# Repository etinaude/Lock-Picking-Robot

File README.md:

# 🔑 Unlocked 🔑

## Introduction

### Background

An open source Lock picking robot. Basically, there are many skeleton keys in use (the most common example is the TSA 007, [which is bad](https://www.youtube.com/watch?v=GhESSMvf_to)). Having one key which can open MANY different locks, especially without the lock owners people knowing it exists [or can be bought on Aliexpres for a pound](https://www.aliexpress.com/item/1005006407379398.html). It is a massive security issue. However, the TSA, locksmiths etc need to open locks in certain situations, and if you make locks easy to open for them, they are easy to open for everyone.

### 🔒 ➡️ 🔑🤖 ➡️ 🔓

So, lock-picking robot!!! The idea behind this robot is that it will be able to open difficult-to-pick locks. However, it takes a bit of time. That means you can get a lock which this robot would take 5 min to pick, but would require hundreds of keys (rather than a set of 7), and waiting with a very overt device by a lock for 5 min is a lot more obvious than unlocking it with a key which makes it look like you own the lock. 

### How it works

It feeds wire through a hollow key to press each pin and brute force all possible combinations. So security pins do not affect it since it is not looking for force feedback. However, more pins, or potential cut depths (entropy) make it take exponentially longer, it takes about 0.7s per combo so a 4 pin/4 cut depth lock would take about 3 min, but 5 pin/5 cut depth would take about 35 min to try all combos. So it's possible to design a lock with many security pins and an annoying keyway, very hard to pick for a human, but relatively quick for this robot.

### TLDR:

For lock sports/locksmiths its a fun toy, and for everyone else an interesting alternative to skeleton keys (and stop using TSA locks)

### Demo

## 💻 Software

### Prerequirements
- Arduino IDE
- Git
- Using [openrb board manager](https://raw.githubusercontent.com/ROBOTIS-GIT/OpenRB-150/master/package_openrb_index.json)
- Arduino SAMD Board Manager
- DYNAMIXEL2Arduino Library

Follow [this guide](https://emanual.robotis.com/docs/en/parts/controller/openrb-150/#development-environment) to get everything set up

The Source Code is in the repo, fully open source, if you make any changes (please do!) keep them open source as well (GPL 3.0 licence)

## ⚡ Electronics

### Components

- Servo Motors - [Dynamixel xl330-m288-t](https://emanual.robotis.com/docs/en/dxl/x/xl330-m288/) 
- Driver Board - [openrb-150](https://emanual.robotis.com/docs/en/parts/controller/openrb-150/)

## ⚙️ Mechanics

Unlocked uses FDM, SLA and DMLS parts for different levels of precision and strength, it uses 0.4mm copper wire to press the pins. More details in the `/3D files` Folder

### Tools Required

- FDM 3D printer
- Vat Polymerization 3D printer (DLP/SLA)
- (Ideally) DMLS 3D printer
- General Hand tools

## 📝 Notes

A new key blank will be needed for a different kind of lock based on the number of pins and the keyway, the current one can be modified to fit this, this should be made out of DMLS steel, companies like JLCPCB can print this, or you can use a SLA part which will likely break a few times so you'll a few spare.

### Future developments

- Include a more robust way to test if the lock is unlocked (for now it tilts slightly from gravity) but a current feedback servo would be better
- Use current feedback to create a set of possible sets or false sets to reduce the number of combos to try
- Before brute force try combing first

## 📄 References

- [Original 1991 Mechanical Patent -  US patent 5,172,578](https://www.researchgate.net/figure/S-A-Bitzioss-1991-design-for-a-Sputnik-decoder-pick-for-pin-tumbler-locks-US_fig9_271020041)
- [A good YouTube video of a design also based on the 1991 patent](https://www.youtube.com/watch?v=QE9MT1LG-PU)
- [Physical lock decoder](https://www.youtube.com/watch?v=CLcOZhq2GjQ)

## 💬 Contact Me

[https://etinaude.dev/contact](https://etinaude.dev/contact)

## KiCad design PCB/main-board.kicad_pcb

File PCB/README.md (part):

# PCBs

KiCad 10 project for the **arm board** in [`main-board/`](main-board/). Each arm of the robot has one: an ESP32-S3 SuperMini drives the arm's brushed DC motor and reads the carriage position from a magnet, and talks to the motherboard over CAN. Etienne calls it the "main board"; the schematic title is "Lock Picking Robot - Arm Board" and the firmware env is `arm`. It is not the motherboard.

## Status

- **Schematic:** v2 rev 7: CAN only (the I²C option and JP1–JP3 are gone) and CAN TX/RX moved to GPIO8/GPIO9. Rev 6 re-assigned the GPIOs for U1 at 0° and added TP3. ERC 0 errors (38 pin-type warnings from the EasyEDA symbols). C14 changed to 100 pF on 2026-10-09 (schematic, PCB and JLC BOM all updated; the BOM lists C1546).
- **PCB: rev 7 routed** (2026-10-07). Zones filled; DRC 0 violations, 0 unconnected, parity clean. U1, U2, U3, J2, CN2, H1/H2, the TPs, the outline and both zones are locked. The heat-sink pad over U2 is still missing and must come back smaller than before (see [Layout to-do](#layout-to-do)).
- **Production files** in [`main-board/production/`](main-board/production/) are from rev 5 and don't match the board. Regenerate before ordering.
- **Firmware isn't ready for this board** ([Known issues](#known-issues)).

## At a glance

| | |
|---|---|
| MCU | ESP32-S3 SuperMini (U1) on 2 × 9-pin 2.54 mm female headers, top side |
| Motor driver | TI DRV8876 (U2), PH/EN mode, 1.0 A current limit |
| Position sensor | Melexis MLX90393 (U3) 3-axis magnetometer, centred over the carriage magnet |
| Bus | TI SN65HVD230 CAN transceiver (U5), 120 Ω termination on solder jumper JP4 |
| Power | 12 V in on CN2 → TPS54202 buck (U4) → 5 V → SuperMini (its LDO makes 3.3 V) |
| Board | 24.7 × 23.75 mm with 1 mm corners, plus R 3.2 mm bulges round the two M2 nuts (24.7 × 28.4 mm overall). 2 layers, 1.6 mm FR4, 1 oz |
| Assembly | Bottom side by JLCPCB (Economic PCBA); top side hand-soldered |

## Connectors and pinout

### CN2: 12 V + bus (AMASS XT30APB(2+2)-M, C53065086)

Vertical male, plug enters from the top. Polarised: make sure the cable and the motherboard use the same pin order.

| Pin | Net |
|---|---|
| 4 | +12V |
| 3 | GND (solid to both pours, carries the motor return) |
| 2 | CANH |
| 1 | CANL |

### J2: motor (JST S2B-PH-K-S, side entry, C173752)

Pin 1 = OUT1, pin 2 = OUT2. The body overhangs the board edge by design.

### U1: SuperMini pin map

| Pin | Net | Use |
|---|---|---|
| GPIO1 | DRV_IPROPI | Motor current, ADC1_CH0, 3.3 V/A |
| GPIO2 / 3 / 4 | MAG_SDA / MAG_SCL / MAG_INT | Magnetometer, I²C address 0x0C |
| GPIO5 / 6 / 7 | EXP_IO5 / EXP_IO6 / EXP_IO7 | Spare, on TP1 / TP2 / TP3 |
| GPIO8 | CAN_TX | CAN TX to U5 (R7 pulls it high) |
| GPIO9 | CAN_RX | CAN RX from U5 |
| GPIO10 | DRV_nFAULT | Driver fault, active low (10 k pull-up) |
| GPIO11 | DRV_nSLEEP | Drive **high** to run |
| GPIO12 | DRV_IN2_PH | Direction |
| GPIO13 | DRV_IN1_EN | PWM |
| TX / RX | | Not used. TX prints the ROM boot log at reset |
| 5V / 3V3 | VBUS / +3V3 | VBUS ≈ 4.7 V after D1 |

The pins follow the layout: U1 sits at 0°, so the left header (GPIO1–7) is next to U3 and the right header (GPIO8–13) is next to U2 and CN2. The reasoning is in [`main-board/layout plan.md`](main-board/layout%20plan.md).

GPIOs are 3.3 V only. Test pads TP1, TP2, TP3, TP5 and TP7 (top, 1.5 mm, labelled) carry IO5, IO6, IO7, 3V3 and GND. TP6 (VBUS, labelled 5V) is on the bottom next to the 5V header pin.

## CAN: U5, JP4

- **U5** is hand-soldered on the top under the SuperMini, so fit and test it **before** soldering the headers.
- **Termination:** JP4 ("TERM") is on the bottom under the XT30, between the bus pins, with R5 (120 Ω) beside it. It is open as made and can be bridged after assembly. The whole bus needs exactly two 120 Ω terminations, at its two ends: bridge JP4 on the two end arms only. On every arm it would be about 17 Ω and the bus won't work. Keep the bit rate modest (250 kbit/s).
- **U5 details:** R7 pulls TXD high so a resetting or flashing arm can't hold the bus dominant (GPIO8 floats during boot). R6 (10 kΩ on Rs) selects slope control. C13 decouples VCC.

## Power

- **U4, TPS54202DDCR** (C191884): 4.5–28 V in, 500 kHz synchronous buck.
  - R8/R9 = 75 kΩ / 10 kΩ set 5.07 V. C14 = 100 pF (C1546) feed-forward across R8: TI's Eq. 16 puts its zero at the loop crossover, 1/(2π × 75 kΩ × 100 pF) ≈ 21 kHz, the same corner as the datasheet's 100 kΩ / 75 pF. Rev 7 had 47 pF (45 kHz, above crossover, little phase boost).
  - L1 = 10 µH FTC252012S100MBCA (C5832376). Stock was low (389 on 2026-10-07); fallback SWPA3015S100MT (C45403, needs a 3 × 3 mm footprint).
  - C1 10 µF 25 V in, C2 100 nF BOOT–SW, C3/C4 2 × 47 µF 6.3 V out. Add a third 47 µF (C16780) if the output rings on a load step.
  - **EN floats** on its internal pull-up. It is rated 7 V max, so never tie it to VIN.
- **D1, 1N5819WS:** feeds the SuperMini's 5 V pin and stops its USB back-feeding the buck while programming. It sits outside the right header next to the 5V pin, so the ESP's supply current stays in the top-right corner, away from U3.
- **+3V3** comes from the SuperMini's LDO and feeds U3, the pull-ups, U5 and the DRV8876 VREF.

## Motor driver: U2, DRV8876RGTR

- PMODE and IMODE tied to GND: PH/EN mode, fixed off-time chopping, auto-retry on overcurrent.
- **Current limit:** R1 = 3.3 kΩ gives I_TRIP = 1.0 A, just above the 12 V N30 gearmotor's stall (just under 1 A measured), and IPROPI reads 3.3 V/A. The ESP32 ADC tops out near 3.1 V, so readings cover 0–0.94 A; a reading pinned at full scale means stalled.
- R1 is an 0805 on hand-solder pads so it's easy to swap: 4.7 kΩ gives 0.70 A, 2.2 kΩ gives 1.5 A.
- C12 (10 nF) filters IPROPI. C5/C6 (100 nF + 22 µF) at VM, C7 on VCP, C8 on CPH–CPL. R2 pulls nFAULT up.

## Magnetometer: U3, MLX90393SLW-ABA-011-RE

I²C mode, address 0x0C (A0 = A1 = GND), INT on MAG_INT. The Hall plates are at the package centre, so U3 is centred over the carriage magnet. R3/R4 are 2.2 kΩ pull-ups; C9/C10 100 nF and C11 10 µF decouple it.

## Layout

### Layout to-do

The full placement plan is in [`main-board/layout plan.md`](main-board/layout%20plan.md).

1. ~~Update PCB from Schematic and place.~~ Done. Placement as built:
   - **Bottom, U2:** C5–C8 along the top edge. R2 right under U2, across nFAULT and VREF (3V3). The strip right of U2 is kept clear for EN/PH and the motor return. R1 (0805) stands on the IPROPI line at (24.3, 29.3), IPROPI pad up, so IPROPI runs straight to C12 and IO1 and MAG_SDA passes underneath.
   - **Bottom, buck:** stacked L1 → C1 → U4. C1 straddles the SW trace, which runs up between C1's pads to L1, so the VIN–GND loop is about 2 mm. C3/C4 sit left of L1, C2 left of U4, and R8/C14/R9 in a row under U4's FB pin.
   - **Bottom, other:** D1 outside the right header, VBUS end towards the 5V pin. TP6 right of C8 next to the 5V pin. U3's caps and pull-ups around U3, with C10 beside pin 8 and R4 on SCL by the CS via. R6 by U5's Rs pin and C13 at (28.9, 39.9) beside U5's VCC via. JP4 and R5 under the XT30 between the bus pins, ≥ 0.98 mm from them.
   - **Top, under the SuperMini:** U5 at 90°: TXD/RXD face IO8/IO9 above the TP row, CANH/CANL leave through the IO10/IO9 gap to the CN2 pins.
2. ~~Route.~~ Done, see [Routing](#routing).
3. **Restore the heat-sink pad, smaller.** It was deleted in the `layout` commit (4722493). The old 28.6–32.4 × 23.45–27.85 rectangle now hits the IPROPI via at (28.45, 27.5) and comes within 0.2 mm of the 3V3 trunk at y 28.15. Use **x 28.95–32.4, y 23.45–27.8** (GND, F.Cu + F.Mask), then refill zones and re-run DRC.
4. Run `scripts/generate_production.py --all` and check the analysis output.

### Routing

| Net group | Layer and path | Width |
|---|---|---|
| 12 V motor feed | Top: CN2 +12V up between H1 and the pad, through the 5V/GND header gap, along the top edge to two vias by C5/C7. VM bus C6–C5–C7 on the bottom, a 0.3 mm link between C5 and C7 into pin 9 | 0.6 mm |
| Motor outputs | Bottom, necked to 0.3 mm at U2. OUT2 runs over the top of J2 pin 1 | 0.5 mm |
| Motor return | GND pours. U2's PGND pins and exposed pad sit in the main bottom pour, which runs straight to CN2's GND pin | — |
| Buck | Bottom. C1 onto VIN/GND, SW up between C1's pads to L1 and under U4 to C2, +5V bar L1–C3–C4 | 0.4–0.6 mm |
| 12 V to the buck | Top through the IO13/IO12 gap, via at (33.55, 32.23), bottom into C1 | 0.4 mm |
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
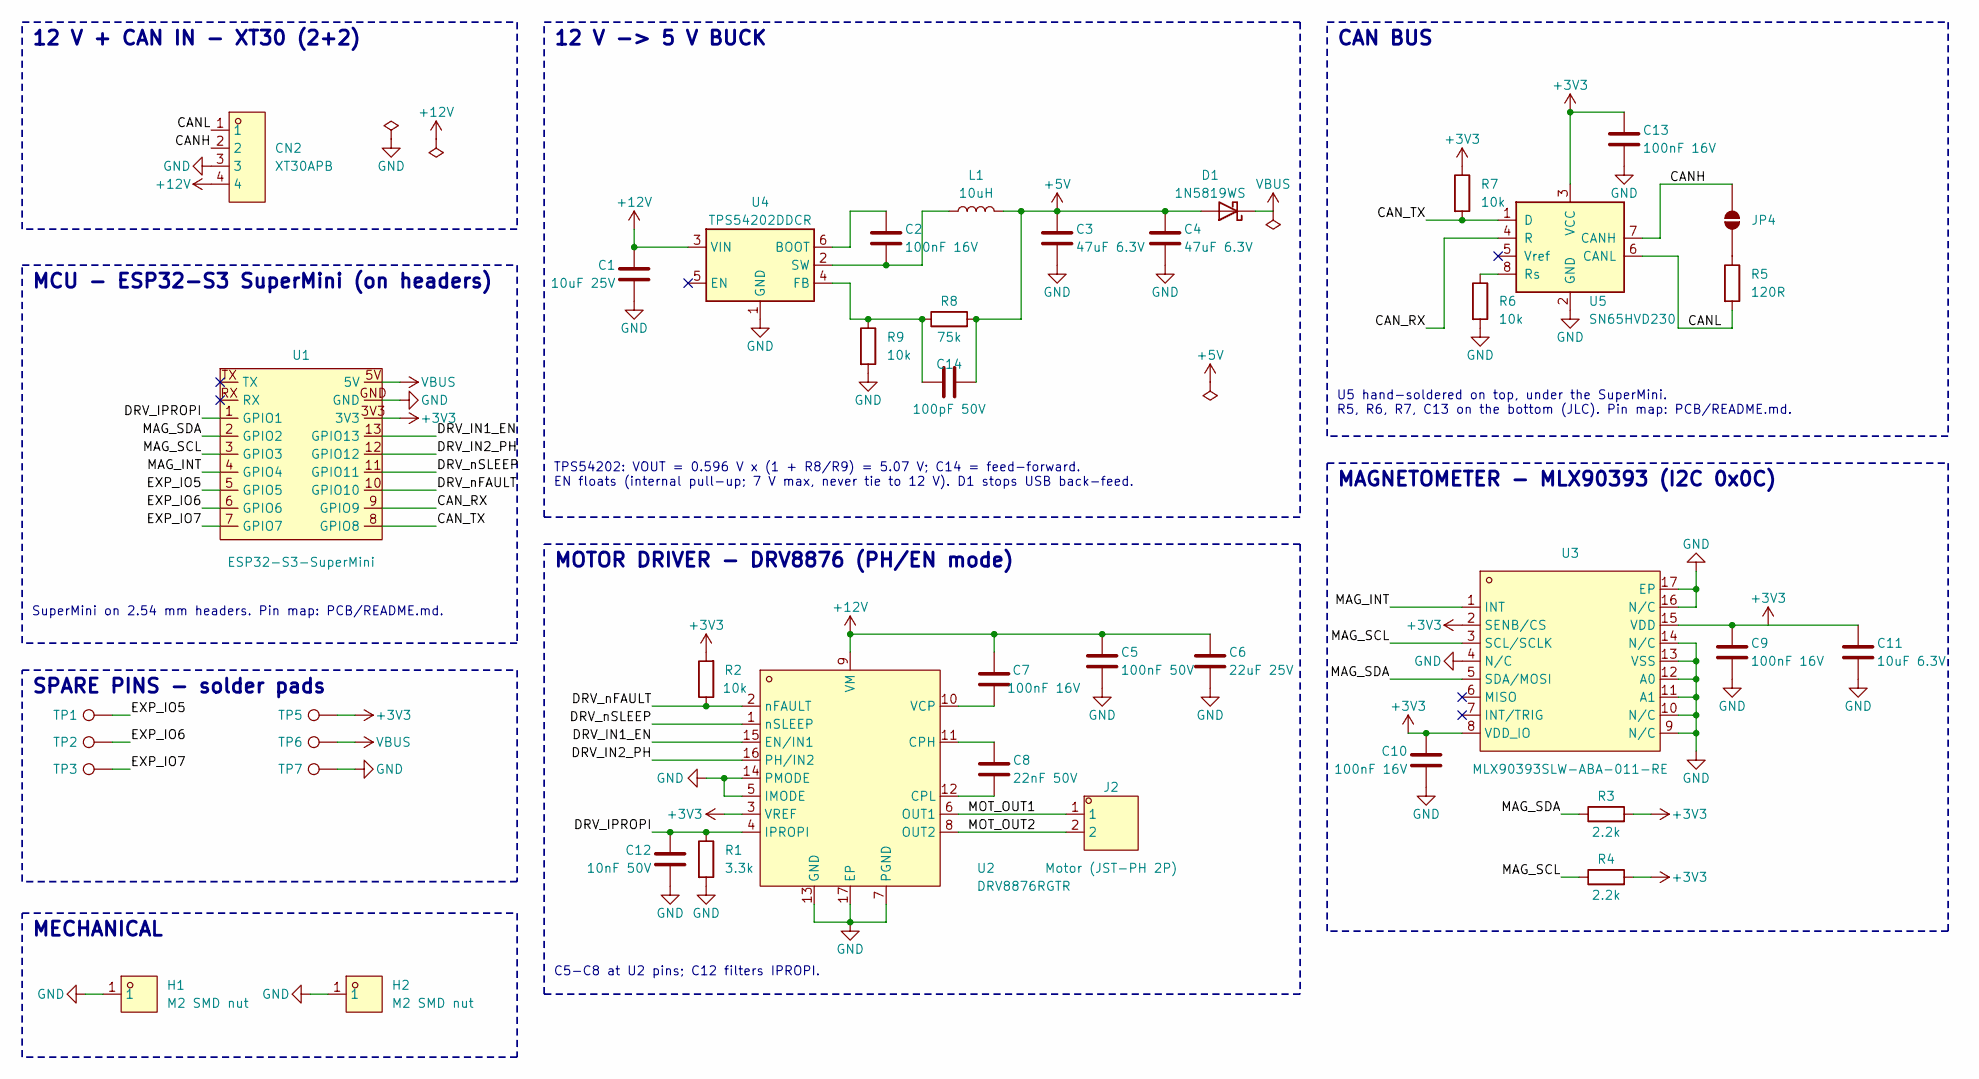
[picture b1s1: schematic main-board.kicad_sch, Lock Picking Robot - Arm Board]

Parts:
C1: 10uF 25V; C_0805_2012Metric; MPN CL21A106KAYNNNE; LCSC Part C15850
C2, C7, C9, C10, C13: 100nF 16V; C_0402_1005Metric; MPN CL05B104KO5NNNC; LCSC Part C1525
C3, C4: 47uF 6.3V; C_0805_2012Metric; MPN CL21A476MQYNNNE; LCSC Part C16780
C5: 100nF 50V; C_0402_1005Metric; MPN CL05B104KB54PNC; LCSC Part C307331
C6: 22uF 25V; C_1206_3216Metric; MPN CL31A226KAHNNNE; LCSC Part C12891
C8: 22nF 50V; C_0402_1005Metric; MPN 0402B223K500NT; LCSC Part C1532
C11: 10uF 6.3V; C_0402_1005Metric; MPN CL05A106MQ5NUNC; LCSC Part C15525
C12: 10nF 50V; C_0402_1005Metric; MPN CL05B103KB5NNNC; LCSC Part C15195
C14: 100pF 50V; C_0402_1005Metric; MPN 0402CG101J500NT; LCSC Part C1546
CN2: XT30APB; CONN-TH_XT30APB; MPN XT30APB(2+2)-M; LCSC Part C53065086
D1: 1N5819WS; D_SOD-323; MPN 1N5819WS; LCSC Part C191023
H1, H2: M2 SMD nut; M2_SMD_nut_SMTSOM225_ring4.2; MPN SMTSOM225BTR; LCSC Part C5301773
J2: Motor (JST-PH 2P); CONN-TH_S2B-PH-K-S-LF-SN; MPN S2B-PH-K-S(LF)(SN); LCSC Part C173752
JP4: 120R term; SolderJumper-2_P1.3mm_Open_RoundedPad1.0x1.5mm
L1: 10uH; L_Changjiang_FTC252012S; MPN FTC252012S100MBCA; LCSC Part C5832376
R1: 3.3k; R_0805_2012Metric_Pad1.20x1.40mm_HandSolder; MPN 0805W8F3301T5E; LCSC Part C26010
R2, R6, R7, R9: 10k; R_0402_1005Metric; MPN 0402WGF1002TCE; LCSC Part C25744
R3, R4: 2.2k; R_0402_1005Metric; MPN 0402WGF2201TCE; LCSC Part C25879
R5: 120R; R_0402_1005Metric; MPN 0402WGF1200TCE; LCSC Part C25079
R8: 75k; R_0402_1005Metric; MPN 0402WGF7502TCE; LCSC Part C25798
TP1, TP2, TP3, TP5, TP6, TP7: Pad; TestPoint_Pad_D1.5mm
U1: ESP32-S3-SuperMini
U2: DRV8876RGTR; QFN-16-1EP_3x3mm_P0.5mm_EP1.68x1.68mm_ThermalVias0.3; MPN DRV8876RGTR; LCSC Part C1852100
U3: MLX90393SLW-ABA-011-RE; VQFN-16_L3.0-W3.0-P0.50-BL-EP1.7; MPN MLX90393SLW-ABA-011-RE; LCSC Part C2649492
U4: TPS54202DDCR; TSOT-23-6; MPN TPS54202DDCR; LCSC Part C191884
U5: SN65HVD230; SOIC-8_3.9x4.9mm_P1.27mm; MPN SN65HVD230DR; LCSC Part C12084

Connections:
+3V3: C9.1, C10.1, C11.1, C13.1, R2.2, R3.2, R4.2, R7.1, TP5.1 (1_1), U1.3V3, U2.3 (VREF), U3.2 (SENB/CS), U3.8 (VDD_IO), U3.15 (VDD), U5.3 (VCC)
+5V: C3.1, C4.1, C14.2, D1.2 (A), L1.2, R8.2
+12V: C1.1, C5.1, C6.1, C7.2, CN2.4, U2.9 (VM), U4.3 (VIN)
/CANH: CN2.2, JP4.1 (A), U5.7 (CANH)
/CANL: CN2.1, R5.2, U5.6 (CANL)
/CAN_RX: U1.9 (GPIO9), U5.4 (R)
/CAN_TX: R7.2, U1.8 (GPIO8), U5.1 (D)
/DRV_IN1_EN: U1.13 (GPIO13), U2.15 (EN/IN1)
/DRV_IN2_PH: U1.12 (GPIO12), U2.16 (PH/IN2)
/DRV_IPROPI: C12.1, R1.1, U1.1 (GPIO1), U2.4 (IPROPI)
/DRV_nFAULT: R2.1, U1.10 (GPIO10), U2.2 (nFAULT)
/DRV_nSLEEP: U1.11 (GPIO11), U2.1 (nSLEEP)
/EXP_IO5: TP1.1 (1_1), U1.5 (GPIO5)
/EXP_IO6: TP2.1 (1_1), U1.6 (GPIO6)
/EXP_IO7: TP3.1 (1_1), U1.7 (GPIO7)
/MAG_INT: U1.4 (GPIO4), U3.1 (INT)
/MAG_SCL: R4.1, U1.3 (GPIO3), U3.3 (SCL/SCLK)
/MAG_SDA: R3.1, U1.2 (GPIO2), U3.5 (SDA/MOSI)
/MOT_OUT1: J2.1, U2.6 (OUT1)
/MOT_OUT2: J2.2, U2.8 (OUT2)
GND: C1.2, C3.2, C4.2, C5.2, C6.2, C9.2, C10.2, C11.2, C12.2, C13.2, CN2.3, H1.1 (1_1), H2.1 (1_1), R1.2, R6.2, R9.2, TP7.1 (1_1), U1.GND, U2.5 (IMODE), U2.7 (PGND), U2.13 (GND), U2.14 (PMODE), U2.17 (EP), U3.4 (N/C), U3.9 (N/C), U3.10 (N/C), U3.11 (A1), U3.12 (A0), U3.13 (VSS), U3.14 (N/C), U3.16 (N/C), U3.17 (EP), U4.1 (GND), U5.2 (GND)
unnamed: JP4.2 (B), R5.1
unnamed: C8.1, U2.11 (CPH)
unnamed: C8.2, U2.12 (CPL)
unnamed: C7.1, U2.10 (VCP)
unnamed: C2.1, U4.6 (BOOT)
unnamed: C14.1, R8.1, R9.1, U4.4 (FB)
unnamed: C2.2, L1.1, U4.2 (SW)
unnamed: R6.1, U5.8 (Rs)
VBUS: D1.1 (K), TP6.1 (1_1), U1.5V

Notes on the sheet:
MOTOR DRIVER - DRV8876 (PH/EN mode)
MAGNETOMETER - MLX90393 (I2C 0x0C)
SuperMini on 2.54 mm headers. Pin map: PCB/README.md.
CAN BUS
SPARE PINS - solder pads
MECHANICAL
U5 hand-soldered on top, under the SuperMini. R5, R6, R7, C13 on the bottom (JLC). Pin map: PCB/README.md.
C5-C8 at U2 pins; C12 filters IPROPI.
12 V + CAN IN - XT30 (2+2)
MCU - ESP32-S3 SuperMini (on headers)
12 V -> 5 V BUCK
TPS54202: VOUT = 0.596 V x (1 + R8/R9) = 5.07 V; C14 = feed-forward. EN floats (internal pull-up; 7 V max, never tie to 12 V). D1 stops USB back-feed.

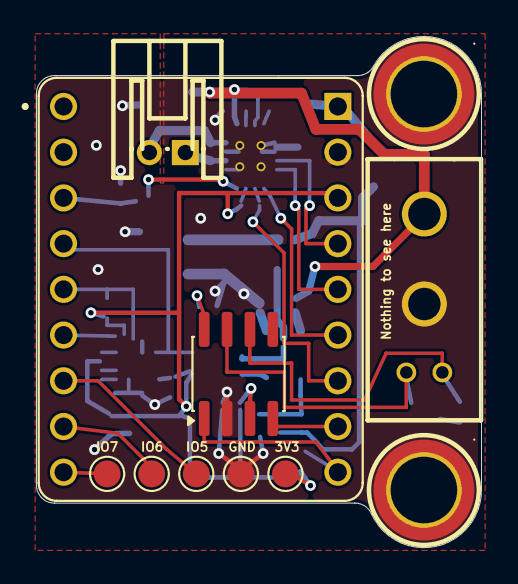
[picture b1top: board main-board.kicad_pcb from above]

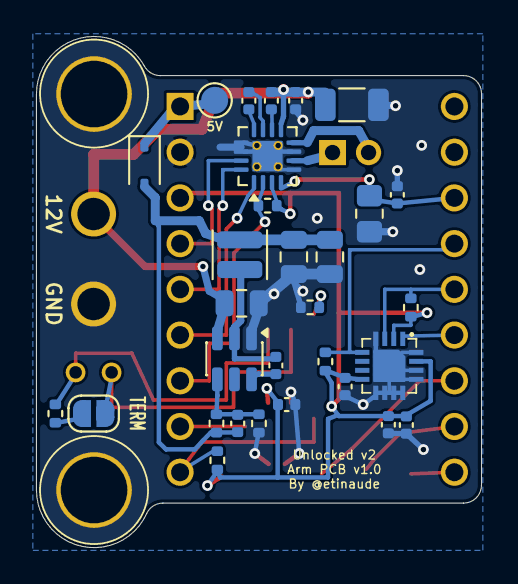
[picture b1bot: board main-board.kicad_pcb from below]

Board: 2 copper layers, 24.7 x 28.4 mm, 41 parts (30 on the bottom side), 30 nets.

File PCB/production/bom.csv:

Designator,Footprint,Quantity,Value,LCSC Part #
C1,0805,1,10uF 25V,C15850
"C10, C2, C7, C9",0402,4,100nF 16V,C1525
C11,0402,1,10uF 6.3V,C15525
C12,0402,1,10nF 50V,C15195
"C3, C4",0805,2,47uF 6.3V,C16780
C5,0402,1,100nF 50V,C307331
C6,1206,1,22uF 25V,C12891
C8,0402,1,22nF 50V,C1532
D1,D_SOD-323,1,1N5819WS,C191023
J1,USB-C_HX-TYPE-C-16PIN_NPTH-pegs,1,USB-C 16P (12V + I2C),C5178539
L1,L_Changjiang_FTC252012S,1,4.7uH,C5832374
R1,0402,1,1.5k 1%,C25867
R2,0402,1,10k,C25744
"R3, R4",0402,2,2.2k,C25879
U2,QFN-16-1EP_3x3mm_P0.5mm_EP1.68x1.68mm_ThermalVias0.3,1,DRV8876RGTR,C1852100
U3,VQFN-16_L3.0-W3.0-P0.50-BL-EP1.7,1,MLX90393SLW-ABA-011-RE,C2649492
U4,TSOT-23-6,1,AP63205WU-7,C2071056

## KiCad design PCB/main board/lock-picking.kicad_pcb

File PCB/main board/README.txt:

KiCad Local History Directory
=============================

This directory contains automatic snapshots of your project files.
KiCad periodically saves copies of your work here, allowing you to
recover from accidental changes or data loss.

You can browse and restore previous versions through KiCad's
File > Local History menu.

To disable this feature:
  Preferences > Common > Project Backup > Enable automatic backups

This directory can be safely deleted if you no longer need the
history, but doing so will permanently remove all saved snapshots.

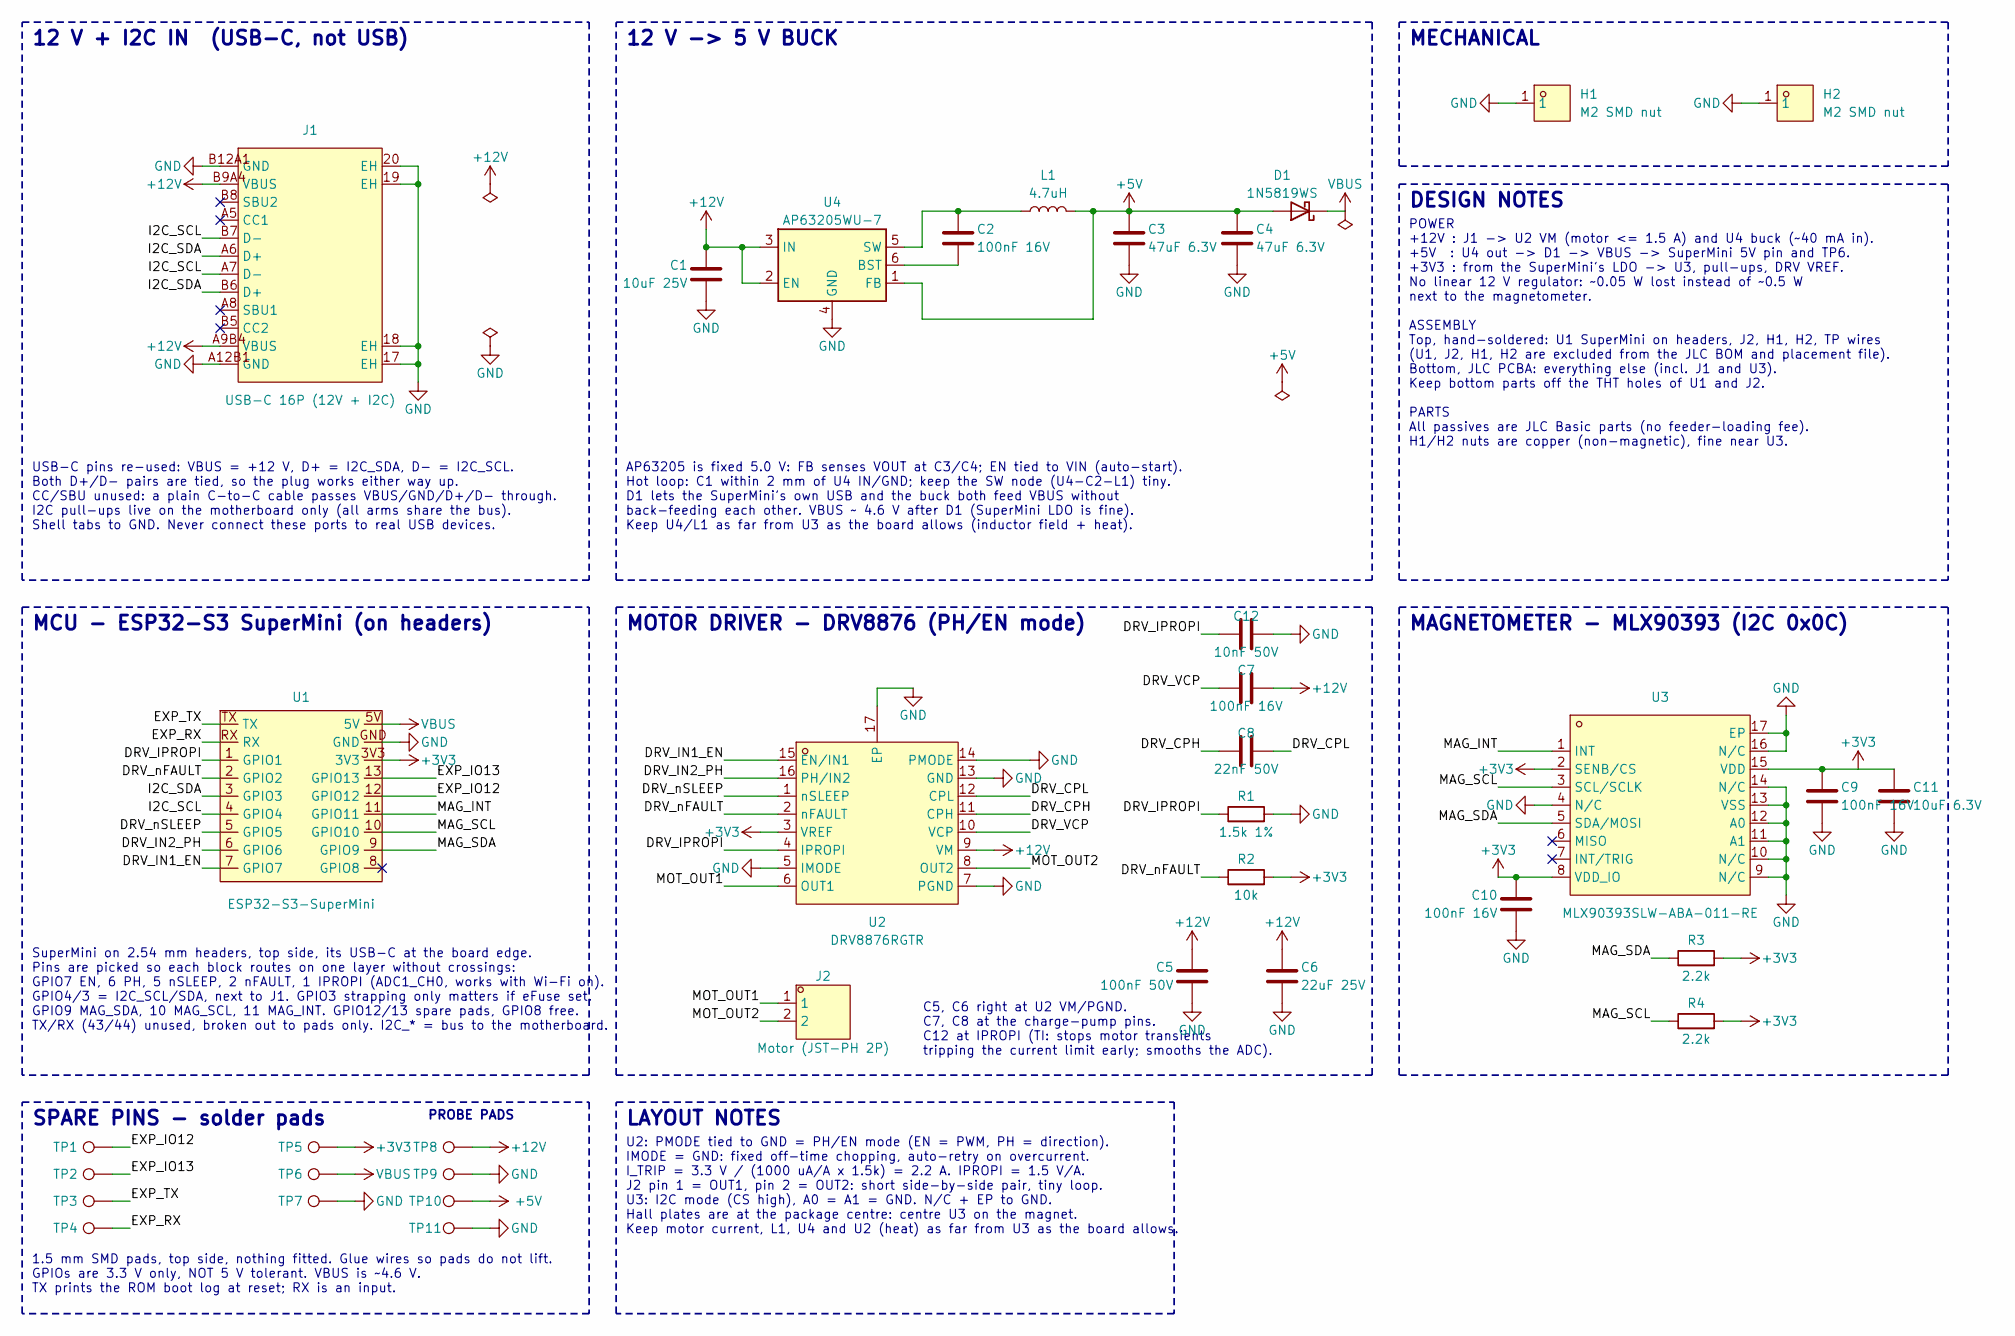
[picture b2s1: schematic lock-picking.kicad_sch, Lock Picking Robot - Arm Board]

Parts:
C1: 10uF 25V; C_0805_2012Metric; MPN CL21A106KAYNNNE; LCSC Part C15850
C2, C7, C9, C10: 100nF 16V; C_0402_1005Metric; MPN CL05B104KO5NNNC; LCSC Part C1525
C3, C4: 47uF 6.3V; C_0805_2012Metric; MPN CL21A476MQYNNNE; LCSC Part C16780
C5: 100nF 50V; C_0402_1005Metric; MPN CL05B104KB54PNC; LCSC Part C307331
C6: 22uF 25V; C_1206_3216Metric; MPN CL31A226KAHNNNE; LCSC Part C12891
C8: 22nF 50V; C_0402_1005Metric; MPN 0402B223K500NT; LCSC Part C1532
C11: 10uF 6.3V; C_0402_1005Metric; MPN CL05A106MQ5NUNC; LCSC Part C15525
C12: 10nF 50V; C_0402_1005Metric; MPN CL05B103KB5NNNC; LCSC Part C15195
D1: 1N5819WS; D_SOD-323; MPN 1N5819WS; LCSC Part C191023
H1, H2: M2 SMD nut; M2_SMD_nut_SMTSOM225_ring4.2; MPN SMTSOM225BTR; LCSC Part C5301773
J1: USB-C 16P (12V + I2C); USB-C_HX-TYPE-C-16PIN_NPTH-pegs; MPN HX TYPE-C 16PIN; LCSC Part C5178539
J2: Motor (JST-PH 2P); CONN-TH_S2B-PH-K-S-LF-SN; MPN S2B-PH-K-S(LF)(SN); LCSC Part C173752
L1: 4.7uH; L_Changjiang_FTC252012S; MPN FTC252012S4R7MBCA; LCSC Part C5832374
R1: 1.5k 1%; R_0402_1005Metric; MPN 0402WGF1501TCE; LCSC Part C25867
R2: 10k; R_0402_1005Metric; MPN 0402WGF1002TCE; LCSC Part C25744
R3, R4: 2.2k; R_0402_1005Metric; MPN 0402WGF2201TCE; LCSC Part C25879
TP1, TP2, TP3, TP4, TP5, TP6, TP7, TP8, TP9: Pad; TestPoint_Pad_D1.5mm
TP10, TP11: Pad; TestPoint_Pad_D1.0mm
U1: ESP32-S3-SuperMini
U2: DRV8876RGTR; QFN-16-1EP_3x3mm_P0.5mm_EP1.68x1.68mm_ThermalVias0.3; MPN DRV8876RGTR; LCSC Part C1852100
U3: MLX90393SLW-ABA-011-RE; VQFN-16_L3.0-W3.0-P0.50-BL-EP1.7; MPN MLX90393SLW-ABA-011-RE; LCSC Part C2649492
U4: AP63205WU-7; TSOT-23-6; MPN AP63205WU-7; LCSC Part C2071056

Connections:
+3V3: C9.1, C10.1, C11.1, R2.2, R3.2, R4.2, TP5.1 (1_1), U1.3V3, U2.3 (VREF), U3.2 (SENB/CS), U3.8 (VDD_IO), U3.15 (VDD)
+5V: C3.1, C4.1, D1.2 (A), L1.2, TP10.1 (1_1), U4.1 (FB)
+12V: C1.1, C5.1, C6.1, C7.2, J1.A9B4 (VBUS), J1.B9A4 (VBUS), TP8.1 (1_1), U2.9 (VM), U4.2 (EN), U4.3 (IN)
/DRV_CPH: C8.1, U2.11 (CPH)
/DRV_CPL: C8.2, U2.12 (CPL)
/DRV_IN1_EN: U1.7 (GPIO7), U2.15 (EN/IN1)
/DRV_IN2_PH: U1.6 (GPIO6), U2.16 (PH/IN2)
/DRV_IPROPI: C12.1, R1.1, U1.1 (GPIO1), U2.4 (IPROPI)
/DRV_VCP: C7.1, U2.10 (VCP)
/DRV_nFAULT: R2.1, U1.2 (GPIO2), U2.2 (nFAULT)
/DRV_nSLEEP: U1.5 (GPIO5), U2.1 (nSLEEP)
/EXP_IO12: TP1.1 (1_1), U1.12 (GPIO12)
/EXP_IO13: TP2.1 (1_1), U1.13 (GPIO13)
/EXP_RX: TP4.1 (1_1), U1.RX
/EXP_TX: TP3.1 (1_1), U1.TX
/I2C_SCL: J1.A7 (D-), J1.B7 (D-), U1.4 (GPIO4)
/I2C_SDA: J1.A6 (D+), J1.B6 (D+), U1.3 (GPIO3)
/MAG_INT: U1.11 (GPIO11), U3.1 (INT)
/MAG_SCL: R4.1, U1.10 (GPIO10), U3.3 (SCL/SCLK)
/MAG_SDA: R3.1, U1.9 (GPIO9), U3.5 (SDA/MOSI)
/MOT_OUT1: J2.1, U2.6 (OUT1)
/MOT_OUT2: J2.2, U2.8 (OUT2)
GND: C1.2, C3.2, C4.2, C5.2, C6.2, C9.2, C10.2, C11.2, C12.2, H1.1, H2.1, J1.17 (EH), J1.18 (EH), J1.19 (EH), J1.20 (EH), J1.A12B1 (GND), J1.B12A1 (GND), R1.2, TP7.1 (1_1), TP9.1 (1_1), TP11.1 (1_1), U1.GND, U2.5 (IMODE), U2.7 (PGND), U2.13 (GND), U2.14 (PMODE), U2.17 (EP), U3.4 (N/C), U3.9 (N/C), U3.10 (N/C), U3.11 (A1), U3.12 (A0), U3.13 (VSS), U3.14 (N/C), U3.16 (N/C), U3.17 (EP), U4.4 (GND)
unnamed: C2.2, U4.6 (BST)
unnamed: C2.1, L1.1, U4.5 (SW)
VBUS: D1.1 (K), TP6.1 (1_1), U1.5V

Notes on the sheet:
USB-C pins re-used: VBUS = +12 V, D+ = I2C_SDA, D- = I2C_SCL. Both D+/D- pairs are tied, so the plug works either way up. CC/SBU unused: a plain C-to-C cable passes VBUS/GND/D+/D- through. I2C pull-ups live on the motherboard only (all arms share the bus). Shell tabs to GND. Never connect these por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
MAGNETOMETER - MLX90393 (I2C 0x0C)
1.5 mm SMD pads, top side, nothing fitted. Glue wires so pads do not lift. GPIOs are 3.3 V only, NOT 5 V tolerant. VBUS is ~4.6 V. TX prints the ROM boot log at reset; RX is an input.
SuperMini on 2.54 mm headers, top side, its USB-C at the board edge. Pins are picked so each block routes on one layer without crossings: GPIO7 EN, 6 PH, 5 nSLEEP, 2 nFAULT, 1 IPROPI (ADC1_CH0, works with Wi-Fi on). GPIO4/3 = I2C_SCL/SDA, next to J1. GPIO3 strapping only matters if eFuse set. GPIO9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
SPARE PINS - solder pads
LAYOUT NOTES
MECHANICAL
C5, C6 right at U2 VM/PGND. C7, C8 at the charge-pump pins. C12 at IPROPI (TI: stops motor transients tripping the current limit early; smooths the ADC).
12 V + I2C IN (USB-C, not USB)
U2: PMODE tied to GND = PH/EN mode (EN = PWM, PH = direction). IMODE = GND: fixed off-time chopping, auto-retry on overcurrent. I_TRIP = 3.3 V / (1000 uA/A x 1.5k) = 2.2 A. IPROPI = 1.5 V/A. J2 pin 1 = OUT1, pin 2 = OUT2: short side-by-side pair, tiny loop. U3: I2C mode (CS high), A0 = A1 = GND. N/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
POWER +12V : J1 -> U2 VM (motor <= 1.5 A) and U4 buck (~40 mA in). +5V : U4 out -> D1 -> VBUS -> SuperMini 5V pin and TP6. +3V3 : from the SuperMini's LDO -> U3, pull-ups, DRV VREF. No linear 12 V regulator: ~0.05 W lost instead of ~0.5 W next to the magnetometer. ASSEMBLY Top, hand-soldered: U1 Su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
MCU - ESP32-S3 SuperMini (on headers)
DESIGN NOTES
12 V -> 5 V BUCK
AP63205 is fixed 5.0 V: FB senses VOUT at C3/C4; EN tied to VIN (auto-start). Hot loop: C1 within 2 mm of U4 IN/GND; keep the SW node (U4-C2-L1) tiny. D1 lets the SuperMini's own USB and the buck both feed VBUS without back-feeding each other. VBUS ~ 4.6 V after D1 (SuperMini LDO is fine). Keep U4/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
MOTOR DRIVER - DRV8876 (PH/EN mode)
PROBE PADS

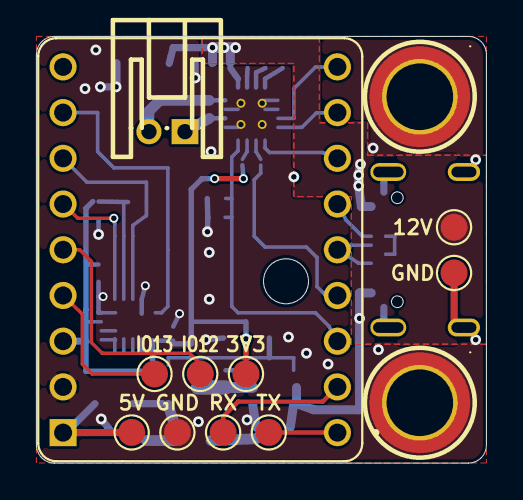
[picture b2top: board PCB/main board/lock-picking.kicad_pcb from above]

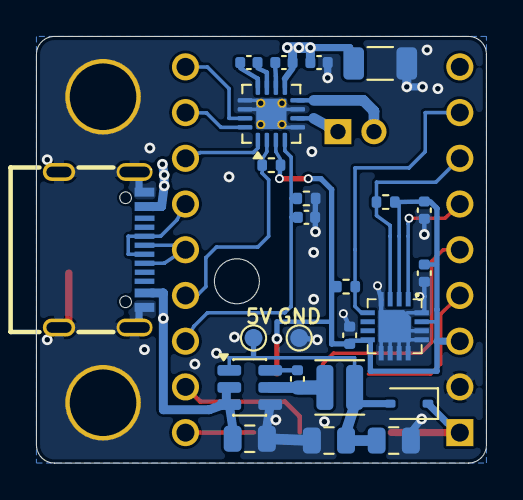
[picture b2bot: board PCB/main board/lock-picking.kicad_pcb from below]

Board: 2 copper layers, 25.0 x 23.7 mm, 37 parts (24 on the bottom side), 26 nets.

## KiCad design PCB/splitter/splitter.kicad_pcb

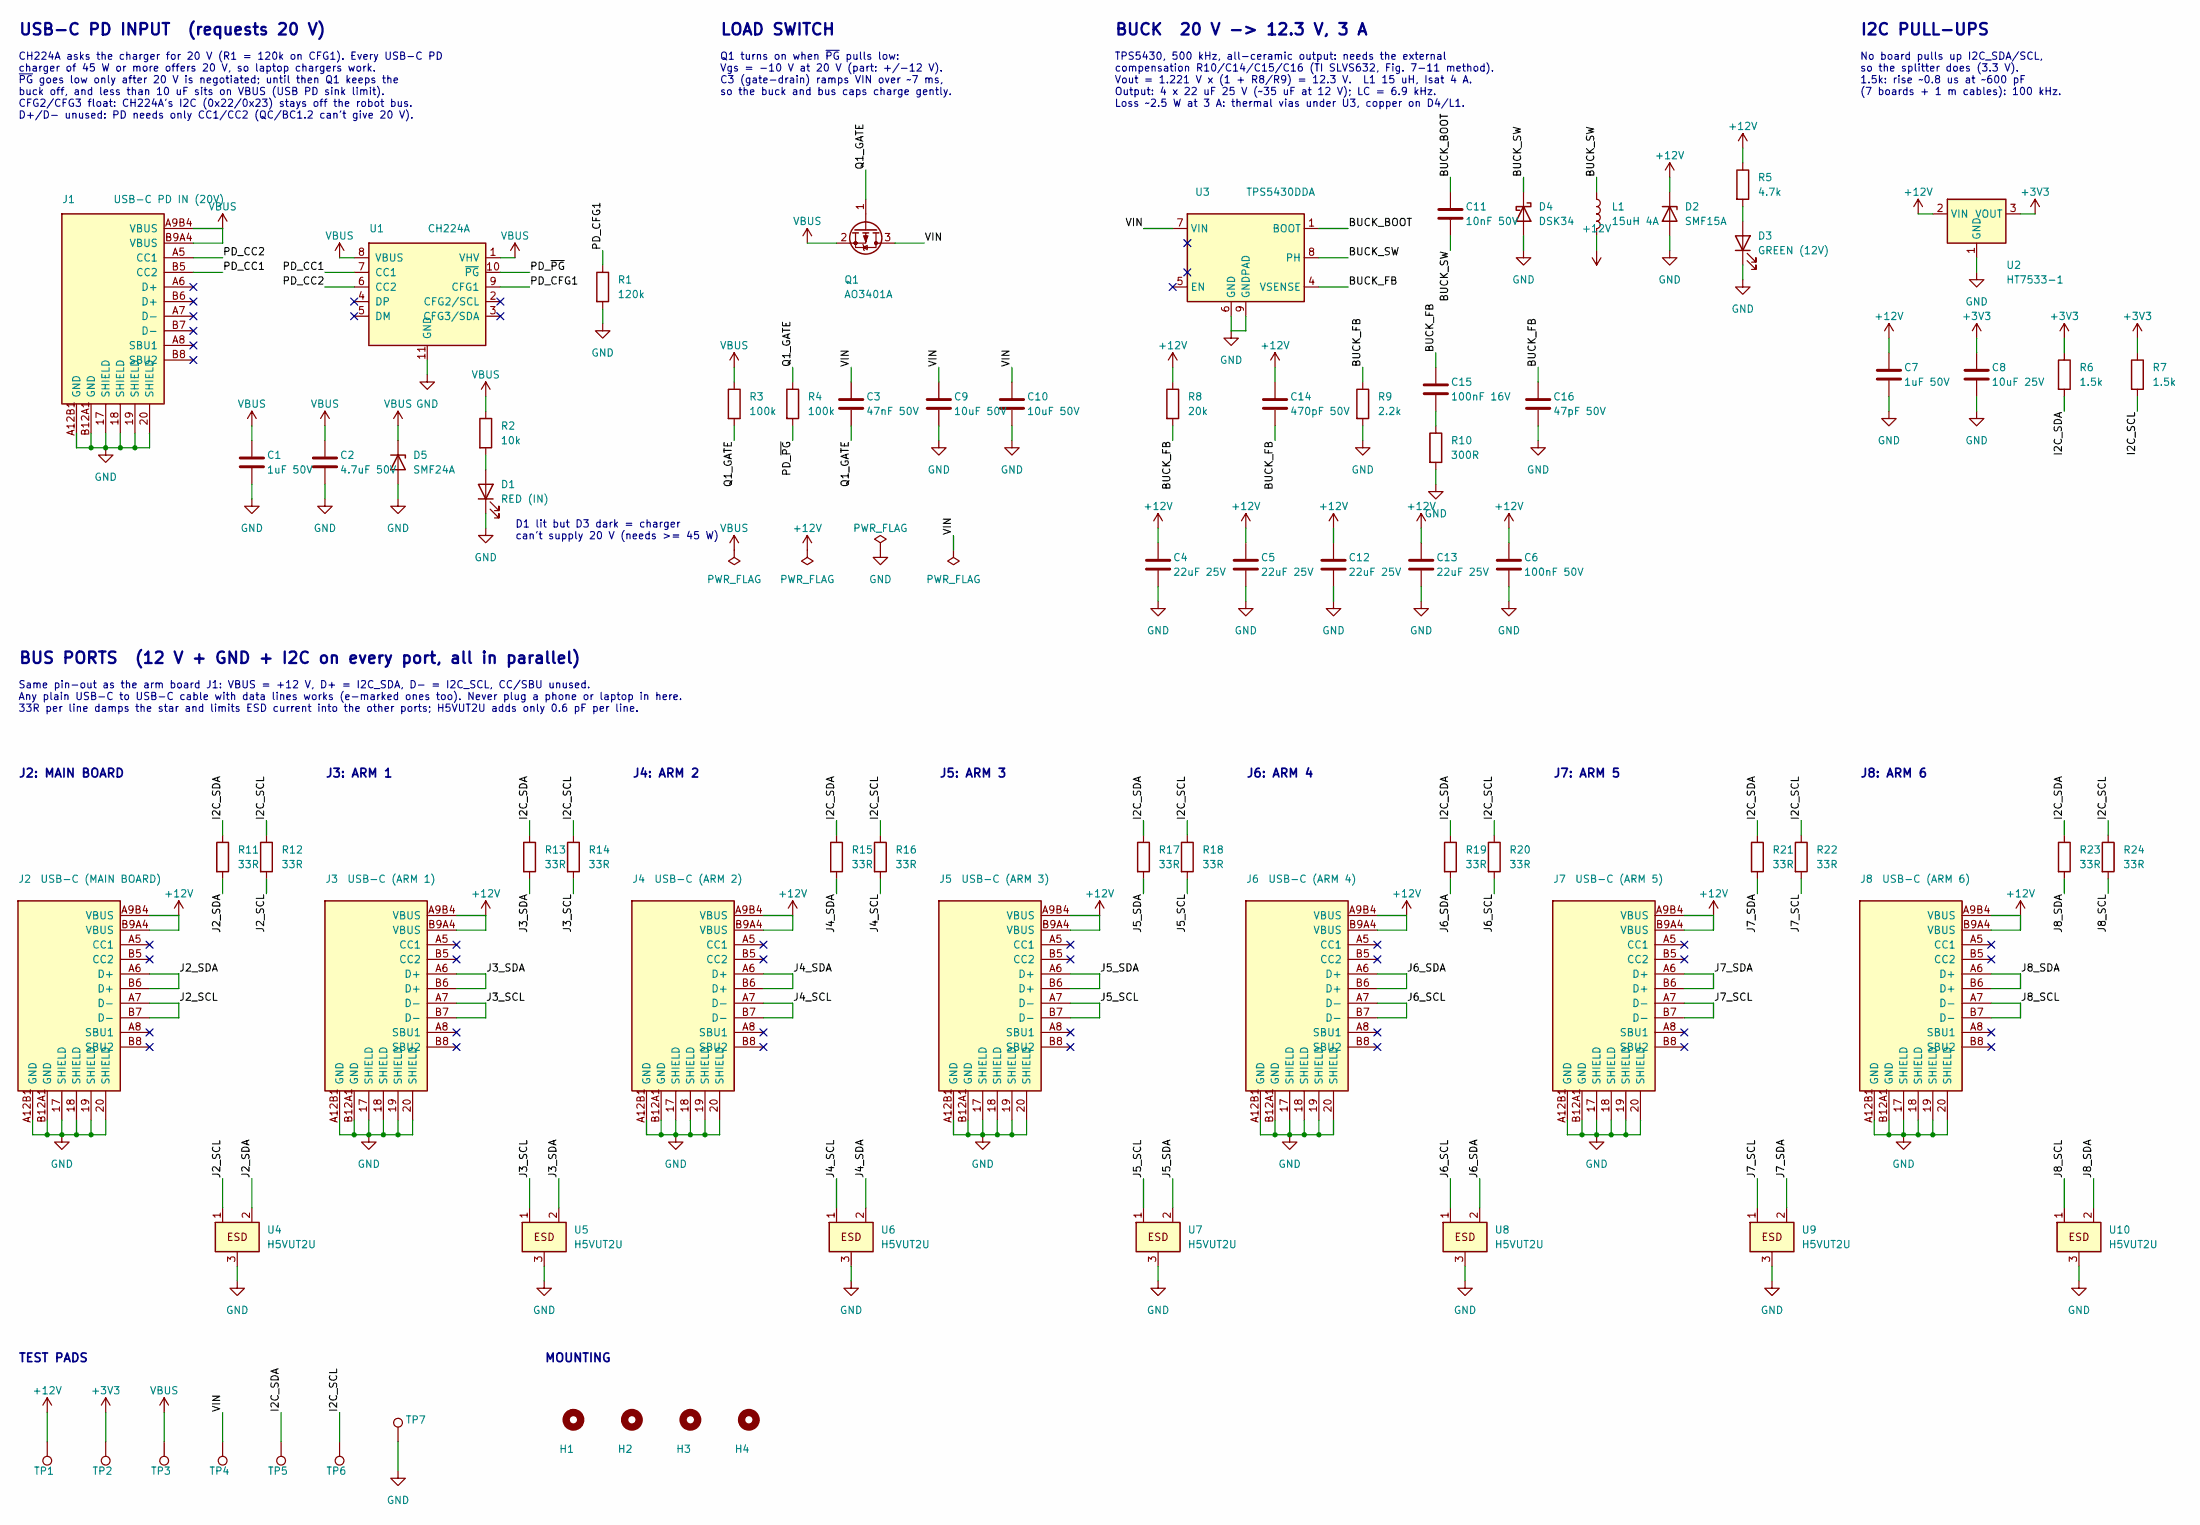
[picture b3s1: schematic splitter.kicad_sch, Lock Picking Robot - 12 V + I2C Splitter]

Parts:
C1, C7: 1uF 50V; C_0603_1608Metric; MPN CL10A105KB8NNNC; LCSC Part C15849
C2: 4.7uF 50V; C_1206_3216Metric; MPN 1206B475K500NT; LCSC Part C29823
C3: 47nF 50V; C_0603_1608Metric; MPN CL10B473KB8NNNC; LCSC Part C1622
C4, C5, C12, C13: 22uF 25V; C_1206_3216Metric; MPN CL31A226KAHNNNE; LCSC Part C12891
C6: 100nF 50V; C_0402_1005Metric; MPN CL05B104KB54PNC; LCSC Part C307331
C8: 10uF 25V; C_0805_2012Metric; MPN CL21A106KAYNNNE; LCSC Part C15850
C9, C10: 10uF 50V; C_1206_3216Metric; MPN CL31A106KBHNNNE; LCSC Part C13585
C11: 10nF 50V; C_0402_1005Metric; MPN CL05B103KB5NNNC; LCSC Part C15195
C14: 470pF 50V; C_0402_1005Metric; MPN 0402B471K500NT; LCSC Part C1537
C15: 100nF 16V; C_0402_1005Metric; MPN CL05B104KO5NNNC; LCSC Part C1525
C16: 47pF 50V; C_0402_1005Metric; MPN 0402CG470J500NT; LCSC Part C1567
D1: RED (IN); LED_0603_1608Metric; MPN KT-0603R; LCSC Part C2286
D2: SMF15A; D_SOD-123F; MPN SMF15A; LCSC Part C19077509
D3: GREEN (12V); LED_0805_2012Metric; MPN KT-0805G; LCSC Part C2297
D4: DSK34; D_SOD-123F; MPN DSK34; LCSC Part C7502709
D5: SMF24A; D_SOD-123F; MPN SMF24A; LCSC Part C19077514
H1, H2, H3, H4: M3; MountingHole_3.2mm_M3
J1: USB-C PD IN (20V); USB-C_HX-TYPE-C-16PIN_NPTH-pegs; MPN HX TYPE-C 16PIN; LCSC Part C5178539
J2: USB-C (MAIN BOARD); USB-C_HX-TYPE-C-16PIN_NPTH-pegs; MPN HX TYPE-C 16PIN; LCSC Part C5178539
J3: USB-C (ARM 1); USB-C_HX-TYPE-C-16PIN_NPTH-pegs; MPN HX TYPE-C 16PIN; LCSC Part C5178539
J4: USB-C (ARM 2); USB-C_HX-TYPE-C-16PIN_NPTH-pegs; MPN HX TYPE-C 16PIN; LCSC Part C5178539
J5: USB-C (ARM 3); USB-C_HX-TYPE-C-16PIN_NPTH-pegs; MPN HX TYPE-C 16PIN; LCSC Part C5178539
J6: USB-C (ARM 4); USB-C_HX-TYPE-C-16PIN_NPTH-pegs; MPN HX TYPE-C 16PIN; LCSC Part C5178539
J7: USB-C (ARM 5); USB-C_HX-TYPE-C-16PIN_NPTH-pegs; MPN HX TYPE-C 16PIN; LCSC Part C5178539
J8: USB-C (ARM 6); USB-C_HX-TYPE-C-16PIN_NPTH-pegs; MPN HX TYPE-C 16PIN; LCSC Part C5178539
L1: 15uH 4A; L_Cjiang_FXL0630; MPN FXL0630-150-M; LCSC Part C177243
Q1: AO3401A; SOT-23; MPN AO3401A; LCSC Part C15127
R1: 120k; R_0402_1005Metric; MPN 0402WGF1203TCE; LCSC Part C25750
R2: 10k; R_0402_1005Metric; MPN 0402WGF1002TCE; LCSC Part C25744
R3, R4: 100k; R_0402_1005Metric; MPN 0402WGF1003TCE; LCSC Part C25741
R5: 4.7k; R_0402_1005Metric; MPN 0402WGF4701TCE; LCSC Part C25900
R6, R7: 1.5k; R_0402_1005Metric; MPN 0402WGF1501TCE; LCSC Part C25867
R8: 20k; R_0402_1005Metric; MPN 0402WGF2002TCE; LCSC Part C25765
R9: 2.2k; R_0402_1005Metric; MPN 0402WGF2201TCE; LCSC Part C25879
R10: 300R; R_0402_1005Metric; MPN 0402WGF3000TCE; LCSC Part C25102
R11, R12, R13, R14, R15, R16, R17, R18, R19, R20, R21, R22, R23, R24: 33R; R_0402_1005Metric; MPN 0402WGF330JTCE; LCSC Part C25105
TP1, TP2, TP3, TP4, TP5, TP6, TP7: Pad; TestPoint_Pad_D1.5mm
U1: CH224A; SSOP-10-1EP_3.9x4.9mm_P1mm_EP2.1x3.3mm; MPN CH224A; LCSC Part C42459160
U2: HT7533-1; SOT-89-3; MPN HT7533-1; LCSC Part C14289
U3: TPS5430DDA; TI_SO-PowerPAD-8_ThermalVias; MPN TPS5430DDAR; LCSC Part C9864
U4, U5, U6, U7, U8, U9, U10: H5VUT2U; SOT-23; MPN H5VUT2U; LCSC Part C20615824

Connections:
+3V3: C8.1, R6.1, R7.1, TP2.1, U2.3 (VOUT)
+12V: C4.1, C5.1, C6.1, C7.1, C12.1, C13.1, C14.1, D2.1 (K), J2.A9B4 (VBUS), J2.B9A4 (VBUS), J3.A9B4 (VBUS), J3.B9A4 (VBUS), J4.A9B4 (VBUS), J4.B9A4 (VBUS), J5.A9B4 (VBUS), J5.B9A4 (VBUS), J6.A9B4 (VBUS), J6.B9A4 (VBUS), J7.A9B4 (VBUS), J7.B9A4 (VBUS), J8.A9B4 (VBUS), J8.B9A4 (VBUS), L1.2, R5.1, R8.1, TP1.1, U2.2 (VIN)
/BUCK_BOOT: C11.1, U3.1 (BOOT)
/BUCK_FB: C14.2, C15.1, C16.1, R8.2, R9.1, U3.4 (VSENSE)
/BUCK_SW: C11.2, D4.1 (K), L1.1, U3.8 (PH)
/I2C_SCL: R7.2, R12.1, R14.1, R16.1, R18.1, R20.1, R22.1, R24.1, TP6.1
/I2C_SDA: R6.2, R11.1, R13.1, R15.1, R17.1, R19.1, R21.1, R23.1, TP5.1
/J2_SCL: J2.A7 (D-), J2.B7 (D-), R12.2, U4.1 (IO1)
/J2_SDA: J2.A6 (D+), J2.B6 (D+), R11.2, U4.2 (IO2)
/J3_SCL: J3.A7 (D-), J3.B7 (D-), R14.2, U5.1 (IO1)
/J3_SDA: J3.A6 (D+), J3.B6 (D+), R13.2, U5.2 (IO2)
/J4_SCL: J4.A7 (D-), J4.B7 (D-), R16.2, U6.1 (IO1)
/J4_SDA: J4.A6 (D+), J4.B6 (D+), R15.2, U6.2 (IO2)
/J5_SCL: J5.A7 (D-), J5.B7 (D-), R18.2, U7.1 (IO1)
/J5_SDA: J5.A6 (D+), J5.B6 (D+), R17.2, U7.2 (IO2)
/J6_SCL: J6.A7 (D-), J6.B7 (D-), R20.2, U8.1 (IO1)
/J6_SDA: J6.A6 (D+), J6.B6 (D+), R19.2, U8.2 (IO2)
/J7_SCL: J7.A7 (D-), J7.B7 (D-), R22.2, U9.1 (IO1)
/J7_SDA: J7.A6 (D+), J7.B6 (D+), R21.2, U9.2 (IO2)
/J8_SCL: J8.A7 (D-), J8.B7 (D-), R24.2, U10.1 (IO1)
/J8_SDA: J8.A6 (D+), J8.B6 (D+), R23.2, U10.2 (IO2)
/PD_CC1: J1.B5 (CC2), U1.7 (CC1)
/PD_CC2: J1.A5 (CC1), U1.6 (CC2)
/PD_CFG1: R1.1, U1.9 (CFG1)
/PD_~PG: R4.2, U1.10 (~PG)
/Q1_GATE: C3.2, Q1.1 (G), R3.2, R4.1
/VIN: C3.1, C9.1, C10.1, Q1.3 (D), TP4.1, U3.7 (VIN)
GND: C1.2, C2.2, C4.2, C5.2, C6.2, C7.2, C8.2, C9.2, C10.2, C12.2, C13.2, C16.2, D1.1 (K), D2.2 (A), D3.1 (K), D4.2 (A), D5.2 (A), J1.17 (SHIELD), J1.18 (SHIELD), J1.19 (SHIELD), J1.20 (SHIELD), J1.A12B1 (GND), J1.B12A1 (GND), J2.17 (SHIELD), J2.18 (SHIELD), J2.19 (SHIELD), J2.20 (SHIELD), J2.A12B1 (GND), J2.B12A1 (GND), J3.17 (SHIELD), J3.18 (SHIELD), J3.19 (SHIELD), J3.20 (SHIELD), J3.A12B1 (GND), J3.B12A1 (GND), J4.17 (SHIELD), J4.18 (SHIELD), J4.19 (SHIELD), J4.20 (SHIELD), J4.A12B1 (GND), J4.B12A1 (GND), J5.17 (SHIELD), J5.18 (SHIELD), J5.19 (SHIELD), J5.20 (SHIELD), J5.A12B1 (GND), J5.B12A1 (GND), J6.17 (SHIELD), J6.18 (SHIELD), J6.19 (SHIELD), J6.20 (SHIELD), J6.A12B1 (GND), J6.B12A1 (GND), J7.17 (SHIELD), J7.18 (SHIELD), J7.19 (SHIELD), J7.20 (SHIELD), J7.A12B1 (GND), J7.B12A1 (GND), J8.17 (SHIELD), J8.18 (SHIELD), J8.19 (SHIELD), J8.20 (SHIELD), J8.A12B1 (GND), J8.B12A1 (GND), R1.2, R9.2, R10.2, TP7.1, U1.11 (GND), U2.1 (GND), U3.6 (GND), U3.9 (GNDPAD), U4.3 (GND), U5.3 (GND), U6.3 (GND), U7.3 (GND), U8.3 (GND), U9.3 (GND), U10.3 (GND)
unnamed: C15.2, R10.1
unnamed: D1.2 (A), R2.2
unnamed: D3.2 (A), R5.2
VBUS: C1.1, C2.1, D5.1 (K), J1.A9B4 (VBUS), J1.B9A4 (VBUS), Q1.2 (S), R2.1, R3.1, TP3.1, U1.1 (VHV), U1.8 (VBUS)

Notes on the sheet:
USB-C PD INPUT (requests 20 V)
CH224A asks the charger for 20 V (R1 = 120k on CFG1). Every USB-C PD charger of 45 W or more offers 20 V, so laptop chargers work. ~{PG} goes low only after 20 V is negotiated; until then Q1 keeps the buck off, and less than 10 uF sits on VBUS (USB PD sink limit). CFG2/CFG3 float: CH224A's I2C (0x2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
D1 lit but D3 dark = charger can't supply 20 V (needs >= 45 W)
LOAD SWITCH
Q1 turns on when ~{PG} pulls low: Vgs = -10 V at 20 V (part: +/-12 V). C3 (gate-drain) ramps VIN over ~7 ms, so the buck and bus caps charge gently.
BUCK 20 V -> 12.3 V, 3 A
TPS5430, 500 kHz, all-ceramic output: needs the external compensation R10/C14/C15/C16 (TI SLVS632, Fig. 7-11 method). Vout = 1.221 V x (1 + R8/R9) = 12.3 V. L1 15 uH, Isat 4 A. Output: 4 x 22 uF 25 V (~35 uF at 12 V); LC = 6.9 kHz. Loss ~2.5 W at 3 A: thermal vias under U3, copper on D4/L1.
I2C PULL-UPS
No board pulls up I2C_SDA/SCL, so the splitter does (3.3 V). 1.5k: rise ~0.8 us at ~600 pF (7 boards + 1 m cables): 100 kHz.
BUS PORTS (12 V + GND + I2C on every port, all in parallel)
Same pin-out as the arm board J1: VBUS = +12 V, D+ = I2C_SDA, D- = I2C_SCL, CC/SBU unused. Any plain USB-C to USB-C cable with data lines works (e-marked ones too). Never plug a phone or laptop in here. 33R per line damps the star and limits ESD current into the other ports; H5VUT2U adds only 0.6 p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
J2: MAIN BOARD
J3: ARM 1
J4: ARM 2
J5: ARM 3
J6: ARM 4
J7: ARM 5
J8: ARM 6
TEST PADS
MOUNTING
